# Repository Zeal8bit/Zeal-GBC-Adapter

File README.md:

## Gameboy (Color) cartridge adapter for Zeal 8-bit Computer

<center>
    
</center>

### This repository is part of [this Youtube video](https://www.youtube.com/watch?v=MxnD7FFjDEM), check it for more information and explanation about this project.

The goal of this project is to create an adapter for connecting any Gameboy or Gameboy Color cartridge to Zeal 8-bit Computer. This will offer the possibility to backup the ROM or RAM (saved data), restore the saved data or even modify the saved data in place.

This repository includes:

* An example program, written in C, to communicate with the adapter. It will read RAM banks from the cartridge and send them through UART. This has been tested with MBC1 and MBC5 cartridges.
* A Python script to run on a host that will receive the data from UART and save them inside a file
* The source code to flash to the PLD (GAL16V8)
* A Kicad (v6) project for the schematics and PCB board

**DISCLAIMER: To prevent any data loss, NEVER plug or unplug the cartridges from the adapter when it is connected to a computer/board that is powered on! I am not responsible for any potential damage caused to the Gameboy cartridge when using the adapter. Use it at your own risk.**

### Requirements

To compile this example you will need:

* python3
  * pyserial package (`pip3 install pyserial`)
* bash
* git (to clone this repo)
* make
* Zeal 8-bit OS source code. Only the `kernel_headers` directory is required, check this repository.
z88dk v2.2 (or later). Only its assembler, z80asm, is strictly required. The latest version of z80asm must be used as earlier versions don't have support for `MACRO`.
To install z88dk, please check out their GitHub project.

### Build

To build the program, define the path to Zeal 8-bit OS, this will let us find the header files used to assemble the example:

```
export ZOS_PATH=/your/path/to/Zeal8bitOS
```

Then simply use the command:

```
cd software
make
```

After compiling, the folder `bin/` in `software/` should contain the binary `dump.bin`. This file can be then loaded to Zeal 8-bit OS through UART thanks to the `load` command.

The binary can also be embedded within the romdisk that will contain both the OS and a read-only file system. For example:

```
cd $ZOS_PATH
export EXTRA_ROMDISK_FILES="/path/to/this/repo/software/bin/dump.bin"
make
```

More info about compiling [Zeal 8-bit OS here](https://github.com/Zeal8bit/Zeal-8-bit-OS#getting-started).

The resulting ROM image can then be provided to an emulator or directly flashed to the computer's ROM that will use it.

### Usage

* On the Zeal 8-bit Computer, execute the dump program from the command line:

    ```
    A:/> ./dump.bin
    ```
    The program should detect the cartridge name, the RAM banks count and their size. The output should look like:
    ```
    POKEMON BLUE
    Cartridge type: 0x3
    Cartridge RAM size: 32 KB
    Ready to send, start the dump script on the host computer
    ```

* **Close the serial monitor on the host computer!** Else, the python script below will not be able to receive characters from the UART.

* On the host, execute the python script, you can use `-h` to have more info about the parameters. For example, to save the file as `PKM.sav` from UART node `/dev/ttyUSB0` with a baudrate of 57600, the following command can be used:

    ```
    python3 dump.py -o PKM.sav -d /dev/ttyUSB0 -b57600 -v
    ```

    The output should look like this:

    ```
    Connecting to /dev/ttyUSB0 with baudrate 57600
    Dumping 4 banks of 8192 bytes, 32768 bytes in total...
    PKM.sav successfully dumped
    ```

## Troubleshooting

Upon execution of the binary on the Zeal 8-bit computer, you may encounter the `Get attr error` issue. This shows that the serial driver in the Zeal 8-bit OS kernel doesn't support setting attributes (raw) via `ioctl`. In that case, you should update your installation of the Zeal 8-bit OS to get the latest version of the serial driver.

## License

Distributed under the Creative Commons Zero v1.0 Universal License. See LICENSE file for more information.

You are free to use it for personal and commercial use, the boilerplate present in each file must not be removed.

The `zeal8bit.com` silkscreen present on the PCB shall be kept.

## Contact

For any suggestion or request, you can contact me at contact [at] zeal8bit [dot] com or on the Discord server https://discord.gg/UzEjwRvBBb

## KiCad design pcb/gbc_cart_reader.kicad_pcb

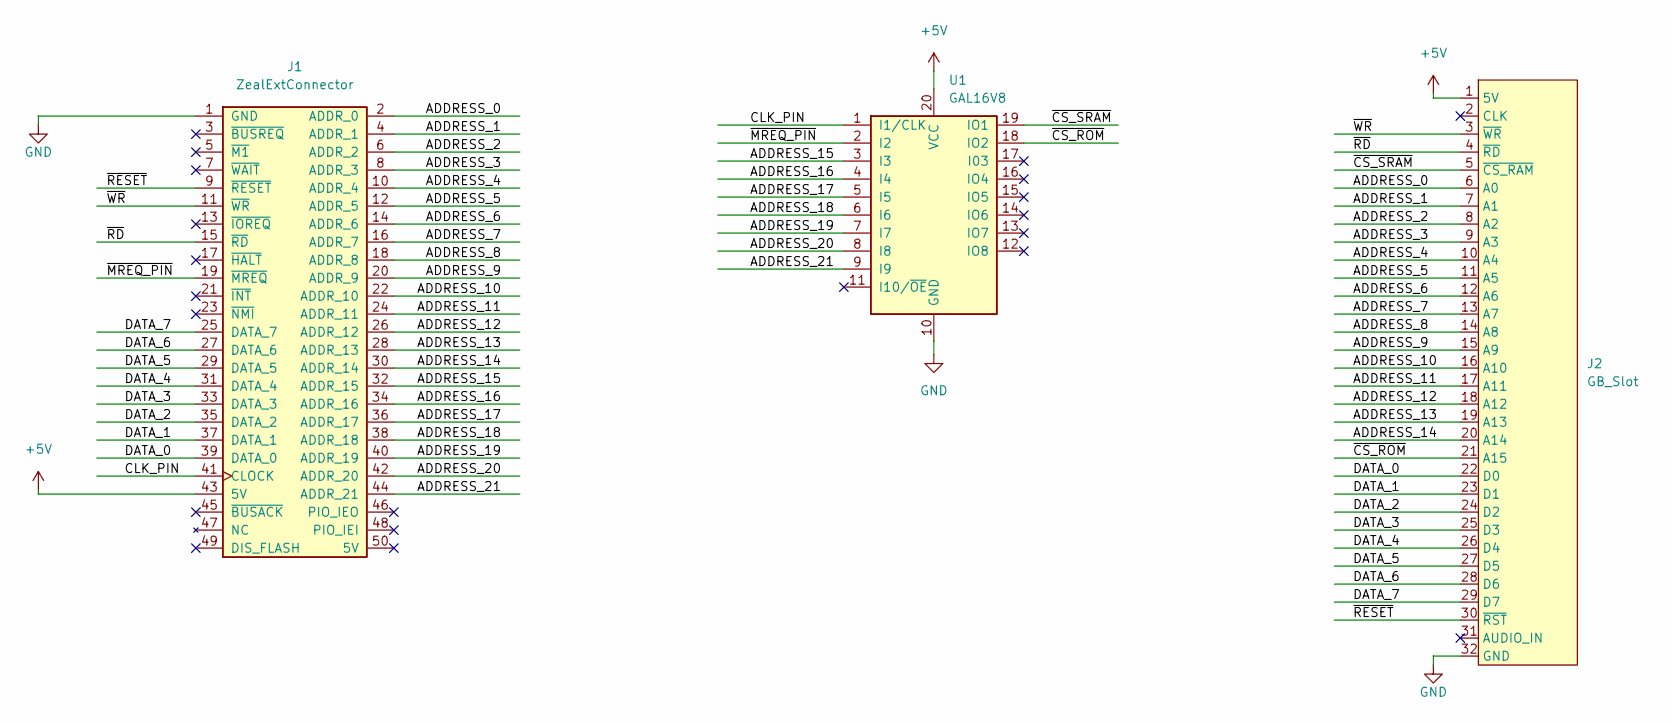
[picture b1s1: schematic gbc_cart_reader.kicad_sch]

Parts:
J1: ZealExtConnector; PinHeader_2x25_P2.54mm_Vertical
J2: GB_Slot; GB Slot
U1: GAL16V8; DIP-20_W7.62mm_Socket

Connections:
+5V: J1.43 (5V), J2.1 (5V), U1.20 (VCC)
/ADDRESS_0: J1.2 (ADDR_0), J2.6 (A0)
/ADDRESS_1: J1.4 (ADDR_1), J2.7 (A1)
/ADDRESS_2: J1.6 (ADDR_2), J2.8 (A2)
/ADDRESS_3: J1.8 (ADDR_3), J2.9 (A3)
/ADDRESS_4: J1.10 (ADDR_4), J2.10 (A4)
/ADDRESS_5: J1.12 (ADDR_5), J2.11 (A5)
/ADDRESS_6: J1.14 (ADDR_6), J2.12 (A6)
/ADDRESS_7: J1.16 (ADDR_7), J2.13 (A7)
/ADDRESS_8: J1.18 (ADDR_8), J2.14 (A8)
/ADDRESS_9: J1.20 (ADDR_9), J2.15 (A9)
/ADDRESS_10: J1.22 (ADDR_10), J2.16 (A10)
/ADDRESS_11: J1.24 (ADDR_11), J2.17 (A11)
/ADDRESS_12: J1.26 (ADDR_12), J2.18 (A12)
/ADDRESS_13: J1.28 (ADDR_13), J2.19 (A13)
/ADDRESS_14: J1.30 (ADDR_14), J2.20 (A14)
/ADDRESS_15: J1.32 (ADDR_15), U1.3 (I3)
/ADDRESS_16: J1.34 (ADDR_16), U1.4 (I4)
/ADDRESS_17: J1.36 (ADDR_17), U1.5 (I5)
/ADDRESS_18: J1.38 (ADDR_18), U1.6 (I6)
/ADDRESS_19: J1.40 (ADDR_19), U1.7 (I7)
/ADDRESS_20: J1.42 (ADDR_20), U1.8 (I8)
/ADDRESS_21: J1.44 (ADDR_21), U1.9 (I9)
/CLK_PIN: J1.41 (CLOCK), U1.1 (I1/CLK)
/DATA_0: J1.39 (DATA_0), J2.22 (D0)
/DATA_1: J1.37 (DATA_1), J2.23 (D1)
/DATA_2: J1.35 (DATA_2), J2.24 (D2)
/DATA_3: J1.33 (DATA_3), J2.25 (D3)
/DATA_4: J1.31 (DATA_4), J2.26 (D4)
/DATA_5: J1.29 (DATA_5), J2.27 (D5)
/DATA_6: J1.27 (DATA_6), J2.28 (D6)
/DATA_7: J1.25 (DATA_7), J2.29 (D7)
/~CS_ROM: J2.21 (A15), U1.18 (IO2)
/~CS_SRAM: J2.5 (~CS_RAM), U1.19 (IO1)
/~MREQ_PIN: J1.19 (~MREQ), U1.2 (I2)
/~RD: J1.15 (~RD), J2.4 (~RD)
/~RESET: J1.9 (~RESET), J2.30 (~RST)
/~WR: J1.11 (~WR), J2.3 (~WR)
GND: J1.1 (GND), J2.32 (GND), U1.10 (GND)

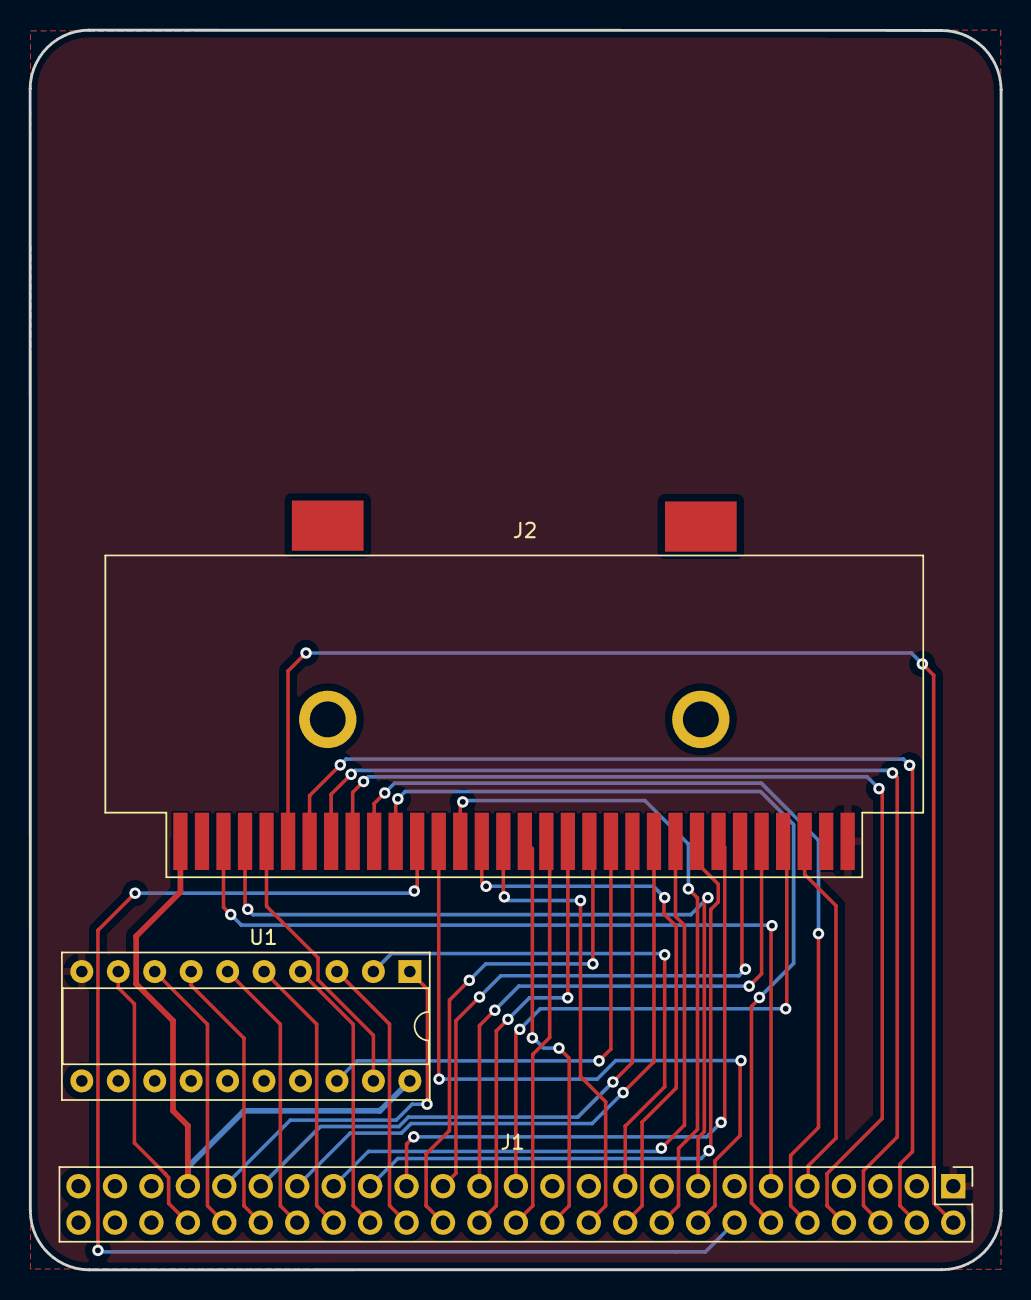
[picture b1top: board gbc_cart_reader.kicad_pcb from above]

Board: 2 copper layers, 67.7 x 86.4 mm, 3 parts (0 on the bottom side), 39 nets.

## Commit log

2023-07-14 Add the PCB, the PLD program and the example software to backup MBC1 and MBC5 Gaemboy games.
2023-07-29 Full MBC1-5 SRAM size and bank info detection.
2023-07-29 Add defines for cartridge types
2023-11-18 Added support to Zeal 8-bit OS implementation using UART as standard output
    This commit brings in a new (Python) script that will ease dump of the cartridge
    save file to the host computer, please check the README.
2023-11-18 Modify output binary name from dump.bin to gbdump.bin
2024-04-22 Provide parameters to `exit` syscall to comply with Zeal 8-bit OS latest API
